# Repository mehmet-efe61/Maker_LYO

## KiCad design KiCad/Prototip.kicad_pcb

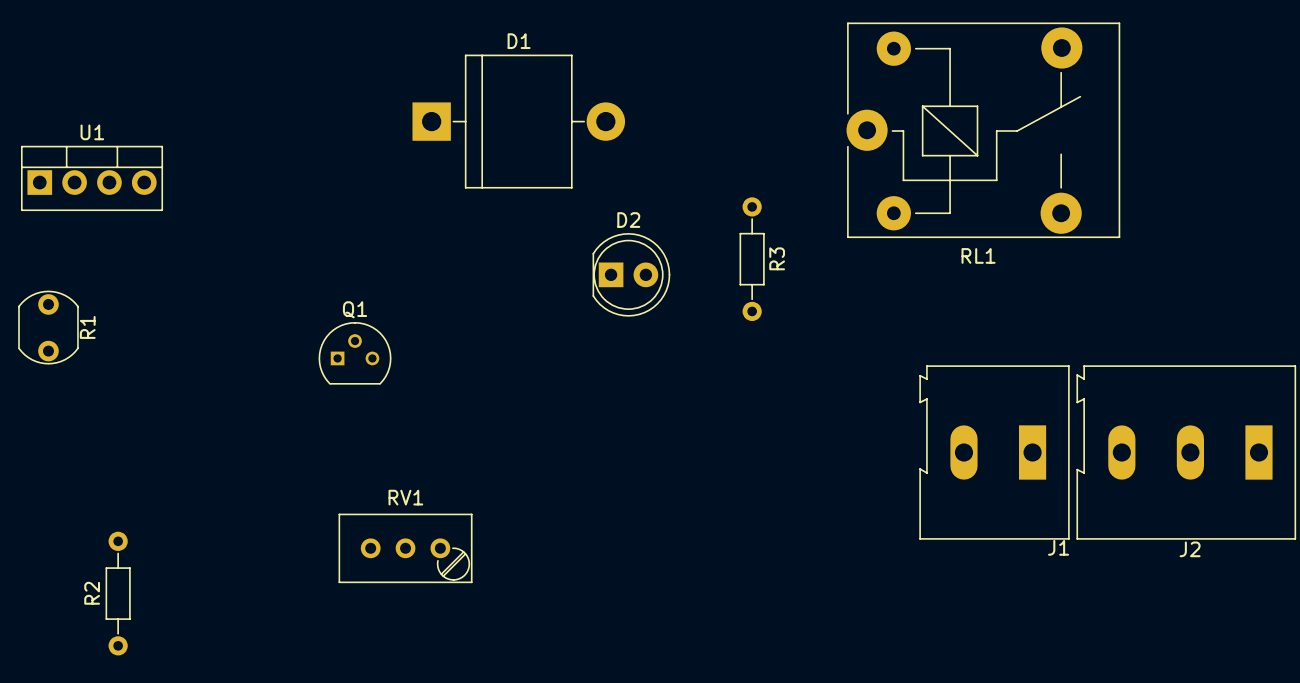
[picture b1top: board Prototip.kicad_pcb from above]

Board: 2 copper layers, 11 parts (0 on the bottom side), 10 nets, no tracks yet.

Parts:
D1: D; D_5KP_P12.70mm_Horizontal
D2: LED; LED_D5.0mm
J1: CONN_01X02; AK300-2
J2: CONN_01X03; AK300-3
Q1: BC237; TO-92_Molded_Narrow
R1: LDR07; Resistor_LDR_5.1x4.3_RM3.4
R2, R3: R; R_Axial_DIN0204_L3.6mm_D1.6mm_P7.62mm_Horizontal
RL1: 5V_RELAY; Relay_SPDT_SANYOU_SRD_Series_Form_C
RV1: POT_TRIM; Potentiometer_Trimmer_Bourns_3296W
U1: 7805; TO-220-4_Vertical

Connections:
COM: J2.2, RL1.3
unnamed: D1.1, R1.1, RL1.1, U1.3
unnamed: D1.2, Q1.1, R3.1
unnamed: D2.1, J1.1, Q1.3, RL1.2, RV1.2, RV1.3, U1.2
unnamed: D2.2, R3.2
unnamed: J1.2, U1.1
unnamed: J2.1, RL1.4
unnamed: J2.3, RL1.5
unnamed: Q1.2, R2.1
unnamed: R1.2, R2.2, RV1.1

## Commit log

2017-07-03 Latest
